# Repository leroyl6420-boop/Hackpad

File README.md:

# Radio Tuner
A custom fidget-Hackpad! I designed the Radio Tuner so that I would have a little radio-tuning fidget wherever I went. Switching between AM and FM changes the target frequency, and the waveform allows you to tell how close you are getting to each target. The Radio Tuner features two push buttons, a 0.91 inch OLED, and an encoder. 

# PCB Design

The Radio Tuner was the first time I had ever created a PCB! To to the constraint of only having two layers, I initially struggled with getting all the ports connected. KiCad was also confusing to navigate. Thankfully, I didn't have a lot of inputs and outputs, and they were all really well documented. For my purposes, the two buttons are for switching between AM and FM radio, and the encoder is for setting the frequency. The OLED is for displaying all those settings and the waveform.

# CAD

The case for the Radio Tuner was very simple. I didn't bother using ai03, instead I just took measurements from KiCad. I made a case and a face. The case has a slot for the USB on the XIAO RP2040, and the face has holes for the keys, the OLED, and the encoder. The face also has engraved text, displaying the Radio Tuner's name and the function of each of the two buttons. 

# Firmware

The firmware was coded using blood, tears, and lots of online tutorials ToT since I don't have any experience nor have I yet received funding, I cannot personally offer any instructions on flashing firmware.

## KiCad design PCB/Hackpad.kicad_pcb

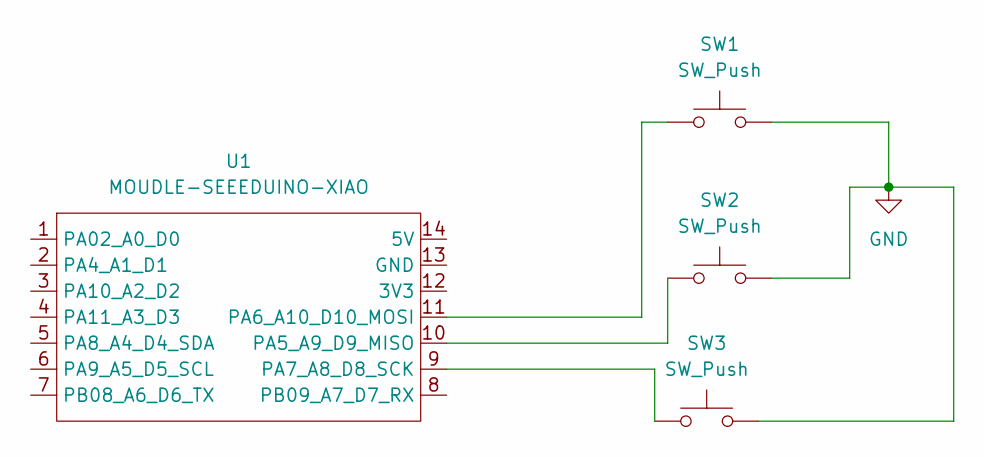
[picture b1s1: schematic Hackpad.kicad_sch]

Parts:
SW1, SW2, SW3: SW_Push; SW_Cherry_MX_1.00u_PCB
U1: MOUDLE-SEEEDUINO-XIAO; XIAO-Generic-Hybrid-14P-2.54-21X17.8MM

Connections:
GND: SW1.2, SW2.2, SW3.2
unnamed: SW2.1, U1.10 (PA5_A9_D9_MISO)
unnamed: SW1.1, U1.11 (PA6_A10_D10_MOSI)
unnamed: SW3.1, U1.9 (PA7_A8_D8_SCK)

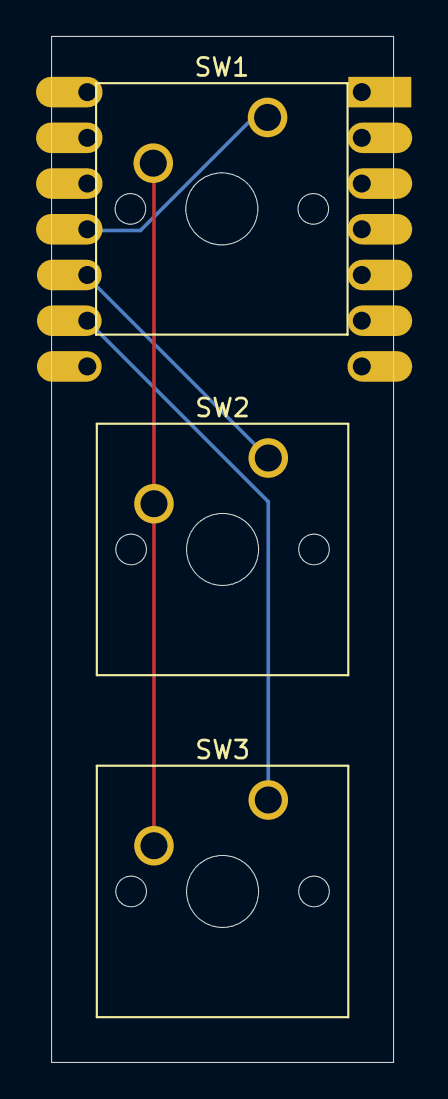
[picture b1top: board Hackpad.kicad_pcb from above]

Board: 2 copper layers, 19.0 x 57.0 mm, 4 parts (1 on the bottom side), 4 nets.
